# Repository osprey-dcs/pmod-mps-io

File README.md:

# Osprey Quartz MPS I/O Daughter Board

A PMOD compatible board providing 4 input and 
4 output bits of optically isolated binary I/O.
Intended to be used with LBL [Marble](https://github.com/BerkeleyLab/Marble).

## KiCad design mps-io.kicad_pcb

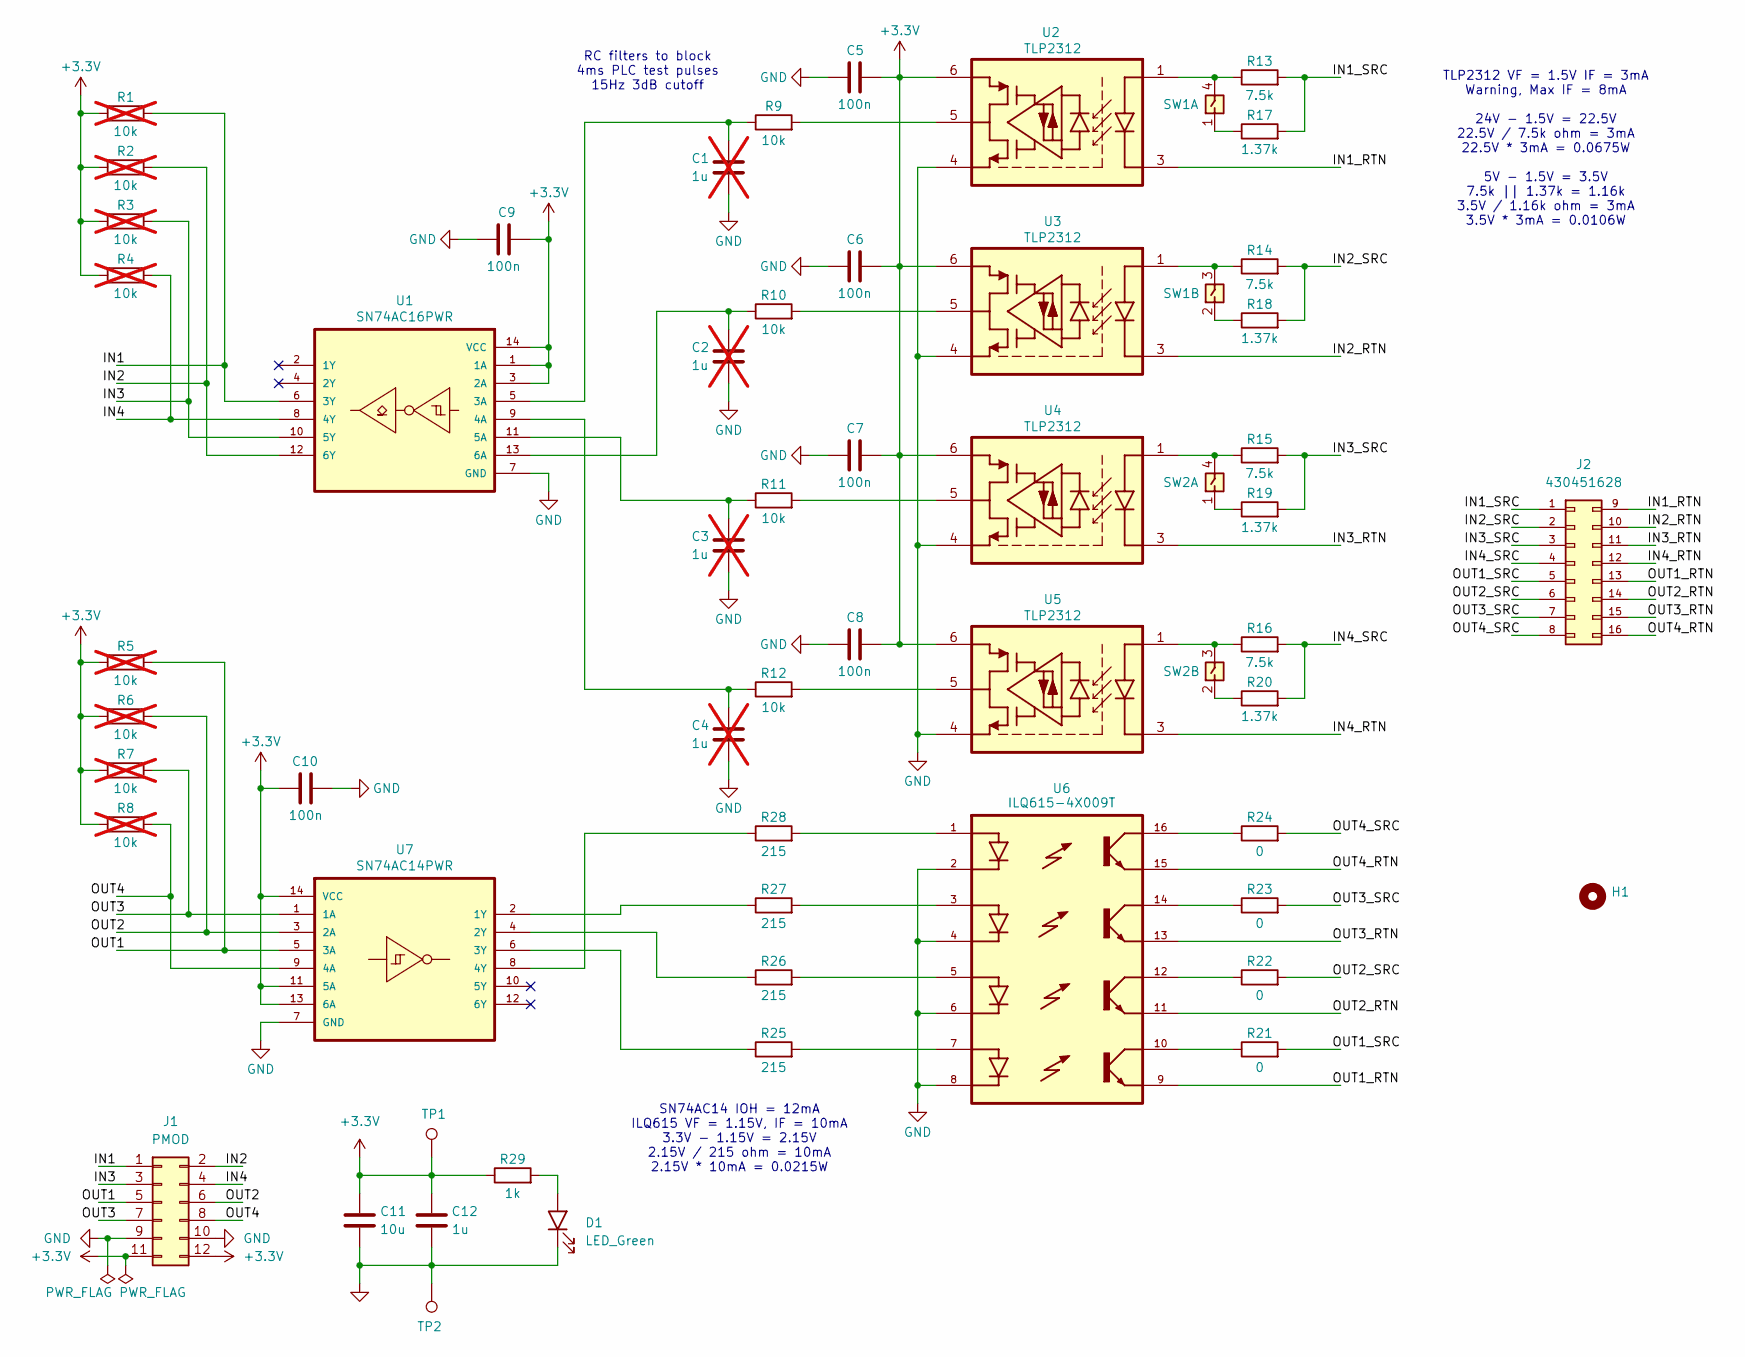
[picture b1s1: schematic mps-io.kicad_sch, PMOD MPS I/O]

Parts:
C1, C2, C3, C4: 1u; C_0603_1608Metric; MPN CC0603KRX7R7BB105; Digikey 311-1446-2-ND; not fitted
C5, C6, C7, C8, C9, C10: 100n; C_0603_1608Metric; MPN CL10B104KB8NNWC; Digikey 1276-1935-2-ND
C11: 10u; C_0805_2012Metric; MPN GRM21BR61E106KA73L; Digikey 490-5523-2-ND
C12: 1u; C_0603_1608Metric; MPN CC0603KRX7R7BB105; Digikey 311-1446-2-ND
D1: LED_Green; LED_0603_1608Metric; MPN APT1608CGCK; Digikey 754-1116
H1: Mounting_Hole_Slot
J1: PMOD; PMOD_2x06_P2.54mm_Mirrored; MPN PH2RA-12-UA; Digikey 2057-PH2RA-12-UA-ND
J2: 430451628; MPN 0430451628; Digikey WM10719-ND
R1, R2, R3, R4, R5, R6, R7, R8: 10k; R_0603_1608Metric; MPN RC0603FR-0710KL; Digikey 311-10.0KHRCT-ND; not fitted
R9, R10, R11, R12: 10k; R_0603_1608Metric; MPN RC0603FR-0710KL; Digikey 311-10.0KHRCT-ND
R13, R14, R15, R16: 7.5k; R_0805_2012Metric; MPN RC0805FR-077K5L; Digikey 311-7.50KCRTR-ND
R17, R18, R19, R20: 1.37k; R_0805_2012Metric; MPN RC0805FR-071K37L; Digikey 311-1.37KCRTR-ND
R21, R22, R23, R24: 0; R_0805_2012Metric; MPN ERJ-6GEY0R00V; Digikey P0.0ATR-ND
R25, R26, R27, R28: 215; R_0603_1608Metric; MPN RC0603FR-07215RL; Digikey 311-215HRTR-ND
R29: 1k; R_0603_1608Metric; MPN RC0603FR-071KL; Digikey 311-1.00KCRTR-ND
SW1, SW2: TDA02H0SB1R; MPN TDA02H0SB1R; Digikey CKN9501CT-ND
TP1: TestPoint; TestPoint_Loop_D1.80mm_Drill1.0mm_Beaded; MPN 5000; Digikey 36-5000-ND
TP2: TestPoint; TestPoint_Loop_D1.80mm_Drill1.0mm_Beaded; MPN 5001; Digikey 36-5001-ND
U1: SN74AC16PWR; SN74AC1xPWR; MPN SN74AC16PWRQ1; Digikey 296-SN74AC16PWRQ1CT-ND
U2, U3, U4, U5: TLP2312; SO6_TLP2312(V4-TPL,E; MPN TLP2312(V4-TPL,E; Digikey 264-TLP2312(V4-TPLECT-ND
U6: ILQ615-4X009T; ILQ615-4X009T_SMD-16; MPN ILQ615-4X009T; Digikey ILQ615-4X009TCT-ND
U7: SN74AC14PWR; SN74AC1xPWR; MPN SN74AC14PWR; Digikey 296-4302-1-ND

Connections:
+3.3V: C5.1, C6.1, C7.1, C8.1, C9.2, C10.2, C11.1, C12.1, J1.11, J1.12, R1.1, R2.1, R3.1, R4.1, R5.1, R6.1, R7.1, R8.1, R29.1, TP1.1, U1.1 (1A), U1.3 (2A), U1.14 (VCC), U2.6, U3.6, U4.6, U5.6, U7.11 (5A), U7.13 (6A), U7.14 (VCC)
/IN1: J1.1, R1.2, U1.6 (3Y)
/IN1_RTN: J2.9, U2.3
/IN1_SRC: J2.1, R13.2, R17.2
/IN2: J1.2, R2.2, U1.12 (6Y)
/IN2_RTN: J2.10, U3.3
/IN2_SRC: J2.2, R14.2, R18.2
/IN3: J1.3, R3.2, U1.10 (5Y)
/IN3_RTN: J2.11, U4.3
/IN3_SRC: J2.3, R15.2, R19.2
/IN4: J1.4, R4.2, U1.8 (4Y)
/IN4_RTN: J2.12, U5.3
/IN4_SRC: J2.4, R16.2, R20.2
/OUT1: J1.5, R5.2, U7.5 (3A)
/OUT1_RTN: J2.13, U6.9
/OUT1_SRC: J2.5, R21.2
/OUT2: J1.6, R6.2, U7.3 (2A)
/OUT2_RTN: J2.14, U6.11
/OUT2_SRC: J2.6, R22.2
/OUT3: J1.7, R7.2, U7.1 (1A)
/OUT3_RTN: J2.15, U6.13
/OUT3_SRC: J2.7, R23.2
/OUT4: J1.8, R8.2, U7.9 (4A)
/OUT4_RTN: J2.16, U6.15
/OUT4_SRC: J2.8, R24.2
GND: C1.2, C2.2, C3.2, C4.2, C5.2, C6.2, C7.2, C8.2, C9.1, C10.1, C11.2, C12.2, D1.1 (K), J1.9, J1.10, TP2.1, U1.7 (GND), U2.4, U3.4, U4.4, U5.4, U6.2, U6.4, U6.6, U6.8, U7.7 (GND)
unnamed: D1.2 (A), R29.2
unnamed: R9.2, U2.5
unnamed: R10.2, U3.5
unnamed: R11.2, U4.5
unnamed: R12.2, U5.5
unnamed: R13.1, SW1.4, U2.1
unnamed: R14.1, SW1.3, U3.1
unnamed: R15.1, SW2.4, U4.1
unnamed: R16.1, SW2.3, U5.1
unnamed: R17.1, SW1.1
unnamed: R18.1, SW1.2
unnamed: R19.1, SW2.1
unnamed: R20.1, SW2.2
unnamed: R21.1, U6.10
unnamed: R22.1, U6.12
unnamed: R23.1, U6.14
unnamed: R24.1, U6.16
unnamed: R25.2, U6.7
unnamed: R26.2, U6.5
unnamed: R27.2, U6.3
unnamed: R28.2, U6.1
unnamed: C1.1, R9.1, U1.5 (3A)
unnamed: C4.1, R12.1, U1.9 (4A)
unnamed: C3.1, R11.1, U1.11 (5A)
unnamed: C2.1, R10.1, U1.13 (6A)
unnamed: R27.1, U7.2 (1Y)
unnamed: R26.1, U7.4 (2Y)
unnamed: R25.1, U7.6 (3Y)
unnamed: R28.1, U7.8 (4Y)

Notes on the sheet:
SN74AC14 IOH = 12mA ILQ615 VF = 1.15V, IF = 10mA 3.3V - 1.15V = 2.15V 2.15V / 215 ohm = 10mA 2.15V * 10mA = 0.0215W
RC filters to block 4ms PLC test pulses 15Hz 3dB cutoff
TLP2312 VF = 1.5V IF = 3mA Warning, Max IF = 8mA 24V - 1.5V = 22.5V 22.5V / 7.5k ohm = 3mA 22.5V * 3mA = 0.0675W 5V - 1.5V = 3.5V 7.5k || 1.37k = 1.16k 3.5V / 1.16k ohm = 3mA 3.5V * 3mA = 0.0106W

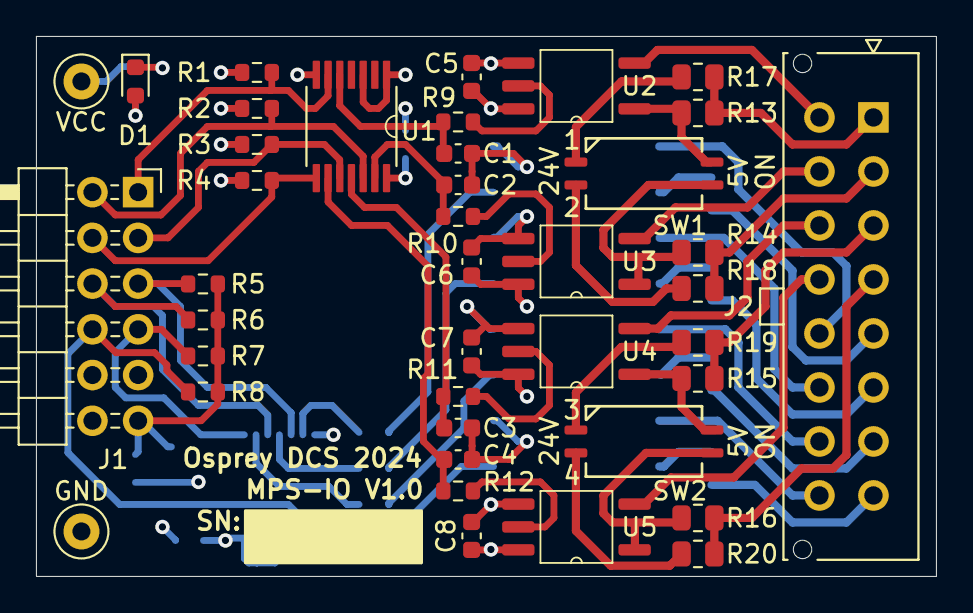
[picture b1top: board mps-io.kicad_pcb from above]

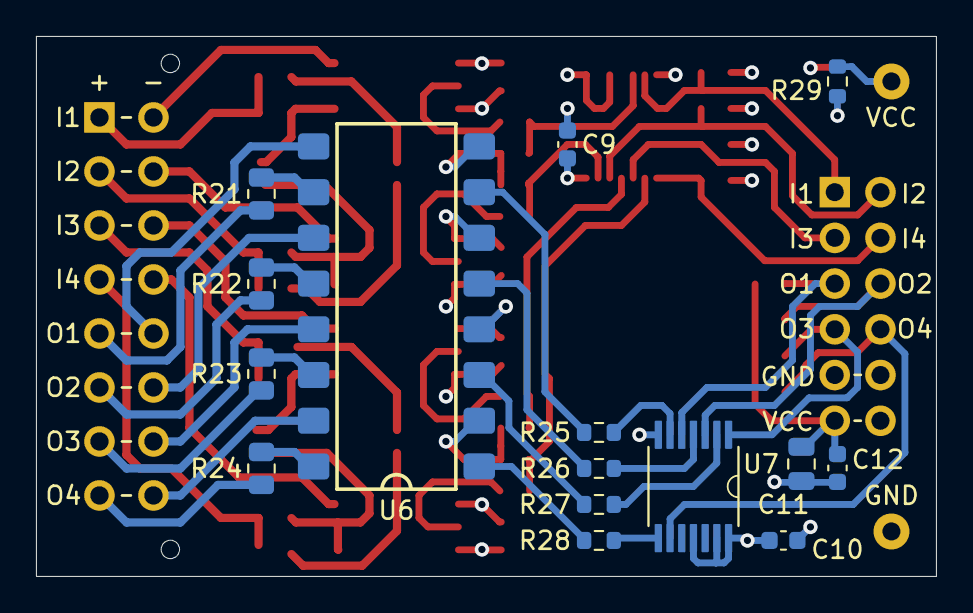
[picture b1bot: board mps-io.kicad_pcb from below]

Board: 4 copper layers, 50.0 x 30.0 mm, 56 parts (15 on the bottom side), 55 nets.

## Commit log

2024-10-31 adjust contraints to quiet DRC
2024-10-31 add missing symbols to 0local
2024-10-31 update pin types to pacify ERC
2024-10-31 ignore project local settings file
2024-10-31 Initial version
2024-10-31 update all symbols from libraries
2024-10-31 fixup footprint assignment
2024-10-31 unix eol
2024-10-31 regenerate step
2024-10-31 fix silkscreen
2024-10-31 update with fab output settings
2024-10-31 add automatic ERC/DRC
2024-10-31 fix PCB PDF script
2024-11-01 Add KiBot automation
2024-11-01 drop scripts
2024-11-01 README
2024-11-04 Final tweaks: J2 pads, D1 603, no mask backoffs, table updates
2024-11-06 test
2024-11-06 Changed slot, moved R5-R8, added/moved slik
2024-11-07 add model for J2
2024-11-07 Add kibot diff
2024-11-07 re-add descriptions and datasheet
2024-11-08 ci: include test points in BoM
    TP1/2 are actual placed components
2024-11-08 GHA update
2024-11-18 add I/O wiring harness
2024-11-30 add picture
2024-12-10 clarify io-cable
2024-12-11 io-cable mirror molex symbol
